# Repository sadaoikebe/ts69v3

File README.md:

# TS69V3 親指シフト入力に使える一体型 65% キーボード

## 特徴

オープンソースの親指シフトキーボードです。

* オープンソース基板（誰でもJLCPCBでオーダー可能！）
* 3Dプリントケース（誰でもJLCPCBで略）
* 一般的なキーボード部品で組み立て可能

## キーボード配列

* US / JP 両対応
* 矢印キーあり
* 対応する親指シフトファームウェアあり [ts69v3 firmware](https://github.com/sadaoikebe/qmk_firmware/tree/master/keyboards/ts69/v3)
* 親指シフト対応、親指キーB下割れ
* 親指キーに3u/2.75u/2.25uのキーキャップの任意の組み合わせが使用できる
* QMK対応

## 物理配列

本PCBで対応する物理配列を以下で解説します。代表的なものは以下の2通りです。

### US配列

<!--
["Esc\n\n~\n`","!\n1","@\n2","#\n3","$\n4","%\n5","^\n6","&\n7","*\n8","(\n9",")\n0","_\n-","+\n=",{w:2},"Backspace","Home"],
[{w:1.5},"Tab","Q","W","E","R","T","Y","U","I","O","P","{\n[","}\n]",{w:1.5},"|\n\\","PgUp"],
[{w:1.75},"Ctrl","A","S","D","F","G","H","J","K","L",":\n;","\"\n'",{w:2.25},"Enter","PgUp"],
[{w:2.25},"Shift","Z","X","C","V","B","N","M","<\n,",">\n.","?\n/",{w:1.75},"Shift","Up","End"],
[{a:7,w:1.25},"",{w:1.25},"",{w:1.25},"",{w:3},"3u 左親指",{w:3},"3u 右親指",{w:1.25},"","","","","",""],
-->

### JP配列
 
<!--
["Esc\n\n~\n`","!\n1","\"\n2","#\n3","$\n4","%\n5","&\n6","'\n7","(\n8",")\n9","\n0","=\n-","~\n^","|\n\\","BS","Home"],
[{w:1.5},"Tab","Q","W","E","R","T","Y","U","I","O","P","`\n@","{\n[",{x:0.25,w:1.25,h:2,w2:1.5,h2:1,x2:-0.25},"Enter","PgUp"],
[{w:1.75},"Ctrl","A","S","D","F","G","H","J","K","L","+\n;","*\n:","}\n]",{x:1.25},"PgDn"],
[{w:2},"Shift","Z","X","C","V","B","N","M","<\n,",">\n.","?\n/","_","Shift","Up","End"],
[{w:1.25},"",{w:1.25},"","","無変換",{w:2.25},"",{w:2.25},"","変換","カタ\nひら","","","","",""],
-->
JP配列のキー数を再現する場合、図のようにShiftの行は左に0.25u移動して、2u左小指シフト/1u右小指シフトを使用します。  
2.25u/1.75uの小指シフトを用いたければ、"_"(アンダースコア)のキーをあきらめてFnキー併用などして入力するようにするとよいでしょう。この場合Shiftの行の物理配列はUS配列と同様になります。  

### 親指シフトキーの選択肢

最下段は使用する親指キーの長さにより割り当てを選択できます。
キーキャップセットによっては、含まれるスペースバーの種類に制約があるけど、できるだけ対応できるようにしました。左右で違う長さの親指キーを使うこともできます。  
2.25uを使用すると、キーが一つ増えます。JP配列の場合は無変換や変換キーを割り当てることを想定しています。US配列の場合はお好みのキーを割り当てられます。

<!--
[{a:7,w:1.25},"",{w:1.25},"",{w:1.25},"",{w:3},"3u 左親指",{w:3},"3u 右親指",{w:1.25},"","","","","",""],
[{w:1.25},"",{w:1.25},"",{w:1.5},"",{w:2.75},"2.75u 左親指",{w:2.75},"2.75u 右親指",{w:1.25},"",{w:1.25},"","","","",""],
[{w:1.25},"",{w:1.25},"","","無変換",{w:2.25},"2.25u 左親指",{w:2.25},"2.25u 左親指","変換","","","","","",""]
-->

### 最上段のBackspaceキー

最上段に2u Backspaceを用いるかわりに、2つのキーを割りあてることができます。最上段にBackspaceを割り当てない場合、一般的に上から2段目のキーにBackspaceを割り当てるようです。(HHKB-likeなレイアウトです)

<!--
["Esc\n\n~\n`","!\n1","@\n2","#\n3","$\n4","%\n5","^\n6","&\n7","*\n8","(\n9",")\n0","_\n-","+\n=",{w:2},"Backspace","Home"],
["Esc","!\n1","@\n2","#\n3","$\n4","%\n5","^\n6","&\n7","*\n8","(\n9",")\n0","_\n-","+\n=","|\n\\","~\n`","Home"],
-->

# BOM

Item |ソース | 数量 |  備考
:--- | :--- | :--- | :---
TS69V3 PCBA | [JLCPCB PCBA](pcb/) | 1 |
ケース | [3D Printed](case/) | 1 | 
定位板 | [Laser Cut Brass](plate/) | 1 | t=1.5mm アクリルでも良いが割れやすい
ヒートセット M3x6mmx4.6mm | [AliEx/淘宝等](https://www.aliexpress.com/item/1005002288716120.html) | 10 | 長さは6mmでなくても良い
M3 円頭六角ボルト 6mm | | 10 |  
クッション 2mm厚 x 60mm x 4mm | | 16 | Poron/EVAフォーム等
Pro Micro | [Shigezone等](https://www.shigezone.com/product/arduino-pro-micro/) | 1 | USB-Cタイプがおすすめ
ピンヘッダ 12pin 2.54ピッチ | 電子工作ショップ等 | 2 |
キースイッチ | AliEx/淘宝/自キ専門店等 | 配列によって69〜73個 | 何でもOK(kailh box 白軸がおすすめ)
2u スタビライザー | AliEx/淘宝/自キ専門店等 | 配列によって2〜5個 | 採用したPlateの種類に応じて Plate Mount / PCB Mountを選択
3u スタビライザー | AliEx/淘宝/自キ専門店等 | 配列によって0〜2個 | 
キーキャップ | AliEx/淘宝/自キ専門店等 | 1set | 3u/2.75u/2.25u等の親指キーが計2つ必要

## 組み立て工程

Pro Microを裏側実装する関係で、実装の順番を間違えると*かなり*面倒
1. 基板にスタビライザーを取り付け
2. 基板にピンヘッダを半田付け
3. 定位板に四隅のキースイッチを通す。Pro Microを実装する面の裏のキー(ESCと1)は2つともキースイッチをハンダ付けする。(以後取り外しが極めて難しい)
4. Pro Microを取り付け、キースイッチを取り付け

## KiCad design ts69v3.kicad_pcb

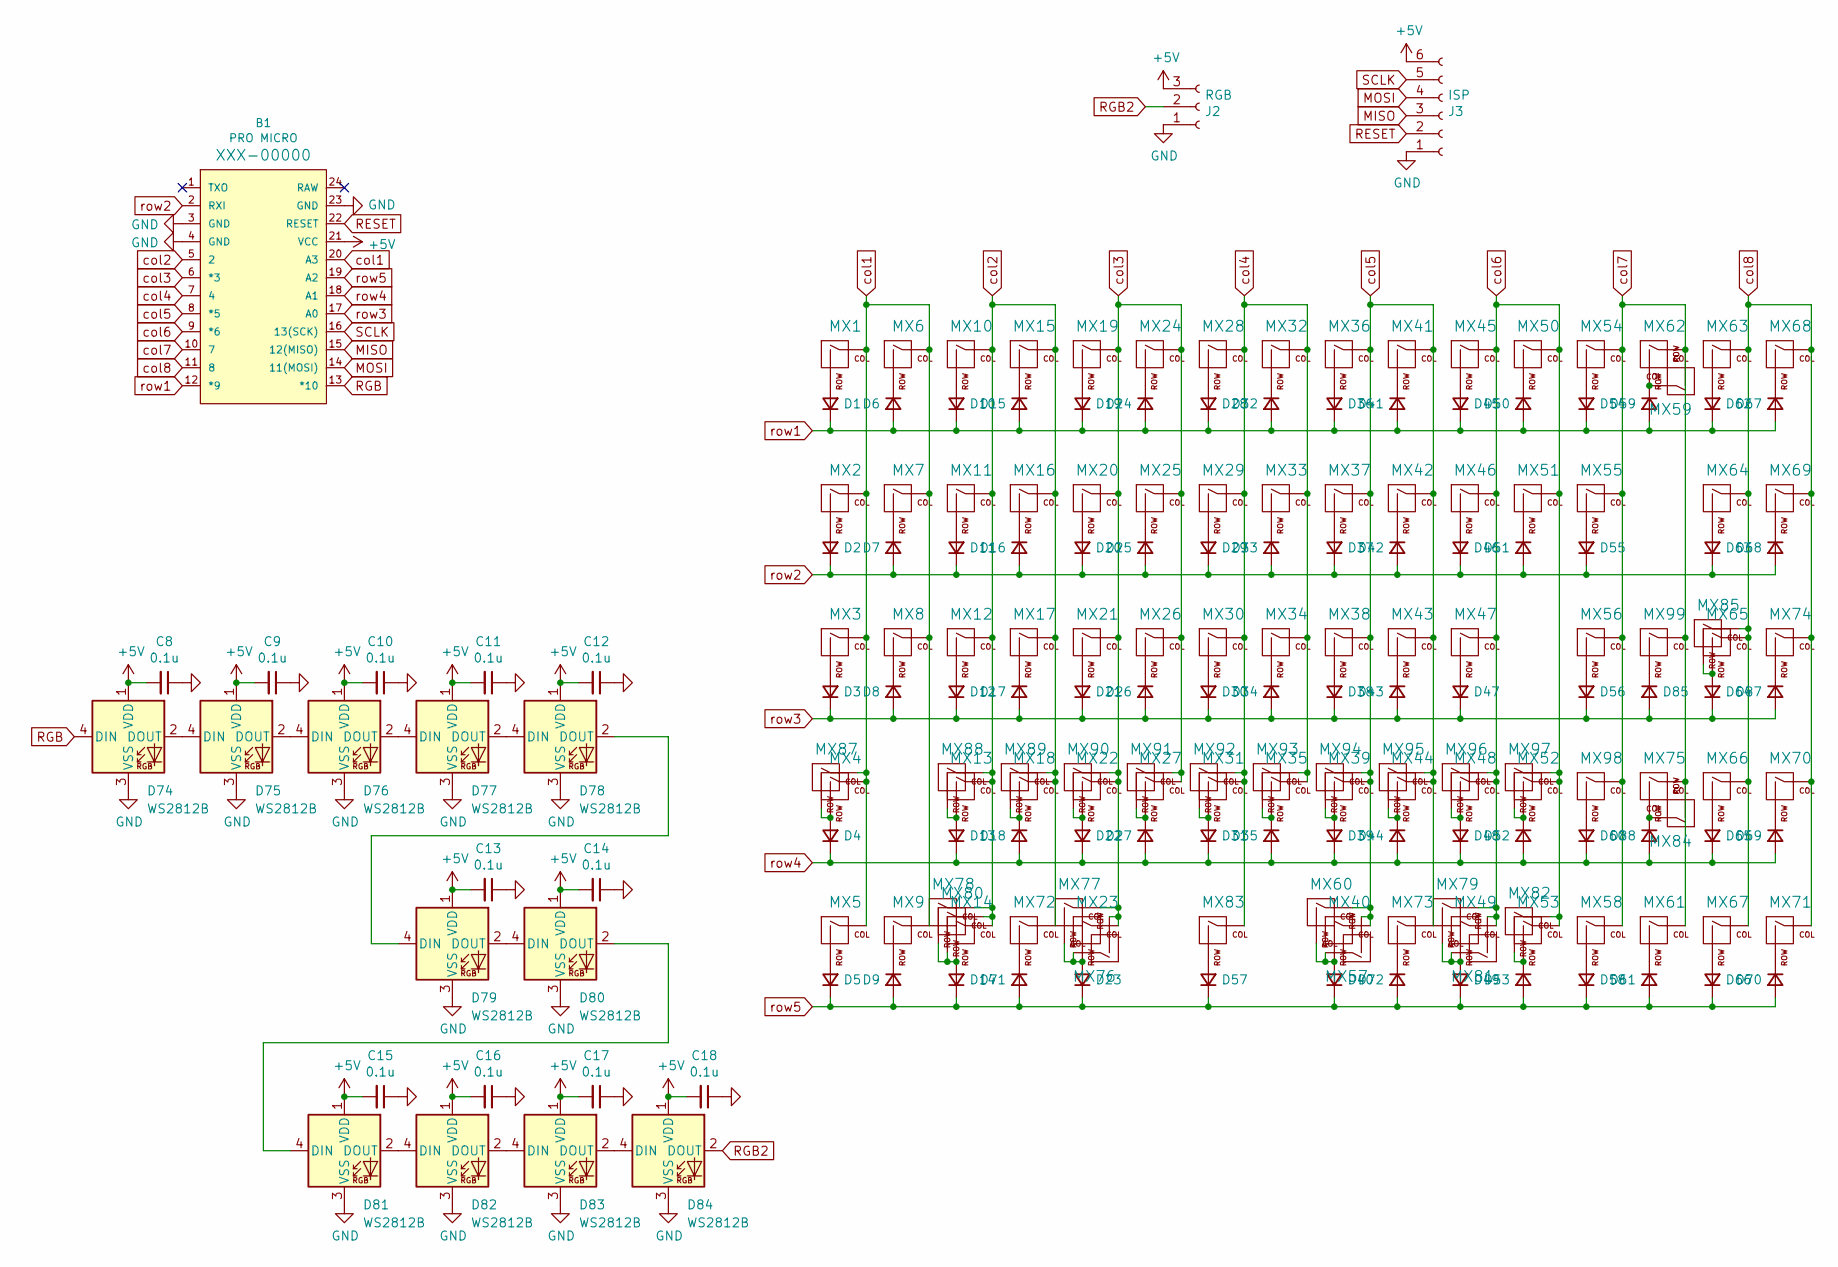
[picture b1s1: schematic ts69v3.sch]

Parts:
B1: PRO MICRO; PROMICRO_CONTHRU
C8, C9, C10, C11, C12, C13, C14, C15, C16, C17, C18: 0.1u; C_0402_1005Metric; LCSC C60474
D1, D2, D3, D4, D5, D6, D7, D8, D9, D10, D11, D12, D13, D14, D15, D16, D17, D18, D19, D20, D21, D22, D23, D24, D25, D26, D27, D28, D29, D30, D31, D32, D33, D34, D35, D36, D37, D38, D39, D40, D41, D42, D43, D44, D45, D46, D47, D48, D49, D50, D51, D52, D53, D54, D55, D56, D57, D58, D59, D61, D62, D63, D64, D65, D66, D67, D68, D69, D70, D71, D72, D87, D88: D; D_SOD-123; LCSC C84367
D60, D85: D; D_SOD-123
D74, D75, D76, D77, D78, D79, D80, D81, D82, D83, D84: WS2812B; LED_WS2812B_PLCC4_5.0x5.0mm_P3.2mm; LCSC C114586
J2: RGB; PinHeader_1x03_P2.00mm_Vertical
J3: ISP; PinHeader_1x06_P2.00mm_Vertical
MX1, MX6, MX7, MX8, MX10, MX11, MX12, MX13, MX15, MX16, MX17, MX18, MX19, MX20, MX21, MX22, MX24, MX25, MX26, MX27, MX28, MX29, MX30, MX31, MX32, MX33, MX34, MX35, MX36, MX37, MX38, MX39, MX41, MX42, MX43, MX44, MX45, MX46, MX47, MX48, MX50, MX51, MX52, MX53, MX54, MX55, MX56, MX58, MX59, MX61, MX63, MX66, MX67, MX68, MX69, MX70, MX71, MX72, MX73, MX74, MX79, MX80, MX84, MX88, MX89, MX90, MX91, MX92, MX93, MX94, MX95, MX96, MX97, MX98, MX99: MX-NoLED; MXOnly-1U-NoLED
MX2, MX64, MX78: MX-NoLED; MXOnly-1.5U-NoLED
MX3, MX75: MX-NoLED; MXOnly-1.75U-NoLED
MX4, MX65: MX-NoLED; MXOnly-2.25U-NoLED
MX5, MX9, MX14, MX49, MX81, MX82: MX-NoLED; MXOnly-1.25U-NoLED
MX23, MX40: MX-NoLED; MXOnly-3U-ReversedStabilizers-NoLED
MX57, MX76: MX-NoLED; MXOnly-2.25U-ReversedStabilizers-NoLED
MX60, MX77: MX-NoLED; MXOnly-2.75U-ReversedStabilizers-NoLED
MX62, MX87: MX-NoLED; MXOnly-2U-NoLED
MX83: MX-NoLED; MXOnly-6.25U-ReversedStabilizers-NoLED
MX85: MX-NoLED; MXOnly-2U-ReversedVerticalStabilizers-NoLED

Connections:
+5V: B1.21 (VCC), C8.2, C9.2, C10.2, C11.2, C12.2, C13.2, C14.2, C15.2, C16.2, C17.2, C18.2, D74.1 (VDD), D75.1 (VDD), D76.1 (VDD), D77.1 (VDD), D78.1 (VDD), D79.1 (VDD), D80.1 (VDD), D81.1 (VDD), D82.1 (VDD), D83.1 (VDD), D84.1 (VDD), J2.3, J3.6
GND: B1.3 (GND), B1.4 (GND), B1.23 (GND), C8.1, C9.1, C10.1, C11.1, C12.1, C13.1, C14.1, C15.1, C16.1, C17.1, C18.1, D74.3 (VSS), D75.3 (VSS), D76.3 (VSS), D77.3 (VSS), D78.3 (VSS), D79.3 (VSS), D80.3 (VSS), D81.3 (VSS), D82.3 (VSS), D83.3 (VSS), D84.3 (VSS), J2.1, J3.1
MISO: B1.15 (12(MISO)), J3.3
MOSI: B1.14 (11(MOSI)), J3.4
unnamed: D1.2 (A), MX1.2 (ROW)
unnamed: D2.2 (A), MX2.2 (ROW)
unnamed: D3.2 (A), MX3.2 (ROW)
unnamed: D4.2 (A), MX4.2 (ROW), MX87.2 (ROW)
unnamed: D5.2 (A), MX5.2 (ROW)
unnamed: D6.1 (K), MX6.2 (ROW)
unnamed: D7.1 (K), MX7.2 (ROW)
unnamed: D8.1 (K), MX8.2 (ROW)
unnamed: D9.1 (K), MX9.2 (ROW)
unnamed: D10.2 (A), MX10.2 (ROW)
unnamed: D11.2 (A), MX11.2 (ROW)
unnamed: D12.2 (A), MX12.2 (ROW)
unnamed: D13.2 (A), MX13.2 (ROW), MX88.2 (ROW)
unnamed: D14.2 (A), MX14.2 (ROW), MX78.2 (ROW), MX80.2 (ROW)
unnamed: D15.1 (K), MX15.2 (ROW)
unnamed: D16.1 (K), MX16.2 (ROW)
unnamed: D17.1 (K), MX17.2 (ROW)
unnamed: D18.1 (K), MX18.2 (ROW), MX89.2 (ROW)
unnamed: D19.2 (A), MX19.2 (ROW)
unnamed: D20.2 (A), MX20.2 (ROW)
unnamed: D21.2 (A), MX21.2 (ROW)
unnamed: D22.2 (A), MX22.2 (ROW), MX90.2 (ROW)
unnamed: D23.2 (A), MX23.2 (ROW), MX76.1 (COL), MX77.2 (ROW)
unnamed: D24.1 (K), MX24.2 (ROW)
unnamed: D25.1 (K), MX25.2 (ROW)
unnamed: D26.1 (K), MX26.2 (ROW)
unnamed: D27.1 (K), MX27.2 (ROW), MX91.2 (ROW)
unnamed: D28.2 (A), MX28.2 (ROW)
unnamed: D29.2 (A), MX29.2 (ROW)
unnamed: D30.2 (A), MX30.2 (ROW)
unnamed: D31.2 (A), MX31.2 (ROW), MX92.2 (ROW)
unnamed: D32.1 (K), MX32.2 (ROW)
unnamed: D33.1 (K), MX33.2 (ROW)
unnamed: D34.1 (K), MX34.2 (ROW)
unnamed: D35.1 (K), MX35.2 (ROW), MX93.2 (ROW)
unnamed: D36.2 (A), MX36.2 (ROW)
unnamed: D37.2 (A), MX37.2 (ROW)
unnamed: D38.2 (A), MX38.2 (ROW)
unnamed: D39.2 (A), MX39.2 (ROW), MX94.2 (ROW)
unnamed: D40.2 (A), MX40.2 (ROW), MX57.1 (COL), MX60.2 (ROW)
unnamed: D41.1 (K), MX41.2 (ROW)
unnamed: D42.1 (K), MX42.2 (ROW)
unnamed: D43.1 (K), MX43.2 (ROW)
unnamed: D44.1 (K), MX44.2 (ROW), MX95.2 (ROW)
unnamed: D45.2 (A), MX45.2 (ROW)
unnamed: D46.2 (A), MX46.2 (ROW)
unnamed: D47.2 (A), MX47.2 (ROW)
unnamed: D48.2 (A), MX48.2 (ROW), MX96.2 (ROW)
unnamed: D49.2 (A), MX49.2 (ROW), MX79.2 (ROW), MX81.1 (COL)
unnamed: D50.1 (K), MX50.2 (ROW)
unnamed: D51.1 (K), MX51.2 (ROW)
unnamed: D52.1 (K), MX52.2 (ROW), MX97.2 (ROW)
unnamed: D53.1 (K), MX53.2 (ROW), MX82.2 (ROW)
unnamed: D54.2 (A), MX54.2 (ROW)
unnamed: D55.2 (A), MX55.2 (ROW)
unnamed: D56.2 (A), MX56.2 (ROW)
unnamed: D57.2 (A), MX83.2 (ROW)
unnamed: D58.2 (A), MX58.2 (ROW)
unnamed: D59.1 (K), MX59.1 (COL), MX62.2 (ROW)
unnamed: D60.2 (A), MX98.2 (ROW)
unnamed: D61.1 (K), MX61.2 (ROW)
unnamed: D62.2 (A), MX63.2 (ROW)
unnamed: D63.2 (A), MX64.2 (ROW)
unnamed: D64.2 (A), MX65.2 (ROW), MX85.2 (ROW)
unnamed: D65.2 (A), MX66.2 (ROW)
unnamed: D66.2 (A), MX67.2 (ROW)
unnamed: D67.1 (K), MX68.2 (ROW)
unnamed: D68.1 (K), MX69.2 (ROW)
unnamed: D69.1 (K), MX70.2 (ROW)
unnamed: D70.1 (K), MX71.2 (ROW)
unnamed: D71.1 (K), MX72.2 (ROW)
unnamed: D72.1 (K), MX73.2 (ROW)
unnamed: D74.2 (DOUT), D75.4 (DIN)
unnamed: D75.2 (DOUT), D76.4 (DIN)
unnamed: D76.2 (DOUT), D77.4 (DIN)
unnamed: D77.2 (DOUT), D78.4 (DIN)
unnamed: D78.2 (DOUT), D79.4 (DIN)
unnamed: D79.2 (DOUT), D80.4 (DIN)
unnamed: D80.2 (DOUT), D81.4 (DIN)
unnamed: D81.2 (DOUT), D82.4 (DIN)
unnamed: D82.2 (DOUT), D83.4 (DIN)
unnamed: D83.2 (DOUT), D84.4 (DIN)
unnamed: D85.1 (K), MX99.2 (ROW)
unnamed: D87.1 (K), MX74.2 (ROW)
unnamed: D88.1 (K), MX75.2 (ROW), MX84.1 (COL)
RESET: B1.22 (RESET), J3.2
RGB: B1.13 (*10), D74.4 (DIN)
RGB2: D84.2 (DOUT), J2.2
SCLK: B1.16 (13(SCK)), J3.5
col1: B1.20 (A3), MX1.1 (COL), MX2.1 (COL), MX3.1 (COL), MX4.1 (COL), MX5.1 (COL), MX6.1 (COL), MX7.1 (COL), MX8.1 (COL), MX9.1 (COL), MX87.1 (COL)
col2: B1.5 (2), MX10.1 (COL), MX11.1 (COL), MX12.1 (COL), MX13.1 (COL), MX14.1 (COL), MX15.1 (COL), MX16.1 (COL), MX17.1 (COL), MX18.1 (COL), MX72.1 (COL), MX78.1 (COL), MX80.1 (COL), MX88.1 (COL), MX89.1 (COL)
col3: B1.6 (*3), MX19.1 (COL), MX20.1 (COL), MX21.1 (COL), MX22.1 (COL), MX23.1 (COL), MX24.1 (COL), MX25.1 (COL), MX26.1 (COL), MX27.1 (COL), MX76.2 (ROW), MX77.1 (COL), MX90.1 (COL), MX91.1 (COL)
col4: B1.7 (4), MX28.1 (COL), MX29.1 (COL), MX30.1 (COL), MX31.1 (COL), MX32.1 (COL), MX33.1 (COL), MX34.1 (COL), MX35.1 (COL), MX83.1 (COL), MX92.1 (COL), MX93.1 (COL)
col5: B1.8 (*5), MX36.1 (COL), MX37.1 (COL), MX38.1 (COL), MX39.1 (COL), MX40.1 (COL), MX41.1 (COL), MX42.1 (COL), MX43.1 (COL), MX44.1 (COL), MX57.2 (ROW), MX60.1 (COL), MX73.1 (COL), MX94.1 (COL), MX95.1 (COL)
col6: B1.9 (*6), MX45.1 (COL), MX46.1 (COL), MX47.1 (COL), MX48.1 (COL), MX49.1 (COL), MX50.1 (COL), MX51.1 (COL), MX52.1 (COL), MX53.1 (COL), MX79.1 (COL), MX81.2 (ROW), MX82.1 (COL), MX96.1 (COL), MX97.1 (COL)
col7: B1.10 (7), MX54.1 (COL), MX55.1 (COL), MX56.1 (COL), MX58.1 (COL), MX59.2 (ROW), MX61.1 (COL), MX62.1 (COL), MX75.1 (COL), MX84.2 (ROW), MX98.1 (COL), MX99.1 (COL)
col8: B1.11 (8), MX63.1 (COL), MX64.1 (COL), MX65.1 (COL), MX66.1 (COL), MX67.1 (COL), MX68.1 (COL), MX69.1 (COL), MX70.1 (COL), MX71.1 (COL), MX74.1 (COL), MX85.1 (COL)
row1: B1.12 (*9), D1.1 (K), D6.2 (A), D10.1 (K), D15.2 (A), D19.1 (K), D24.2 (A), D28.1 (K), D32.2 (A), D36.1 (K), D41.2 (A), D45.1 (K), D50.2 (A), D54.1 (K), D59.2 (A), D62.1 (K), D67.2 (A)
row2: B1.2 (RXI), D2.1 (K), D7.2 (A), D11.1 (K), D16.2 (A), D20.1 (K), D25.2 (A), D29.1 (K), D33.2 (A), D37.1 (K), D42.2 (A), D46.1 (K), D51.2 (A), D55.1 (K), D63.1 (K), D68.2 (A)
row3: B1.17 (A0), D3.1 (K), D8.2 (A), D12.1 (K), D17.2 (A), D21.1 (K), D26.2 (A), D30.1 (K), D34.2 (A), D38.1 (K), D43.2 (A), D47.1 (K), D56.1 (K), D64.1 (K), D85.2 (A), D87.2 (A)
row4: B1.18 (A1), D4.1 (K), D13.1 (K), D18.2 (A), D22.1 (K), D27.2 (A), D31.1 (K), D35.2 (A), D39.1 (K), D44.2 (A), D48.1 (K), D52.2 (A), D60.1 (K), D65.1 (K), D69.2 (A), D88.2 (A)
row5: B1.19 (A2), D5.1 (K), D9.2 (A), D14.1 (K), D23.1 (K), D40.1 (K), D49.1 (K), D53.2 (A), D57.1 (K), D58.1 (K), D61.2 (A), D66.1 (K), D70.2 (A), D71.2 (A), D72.2 (A)

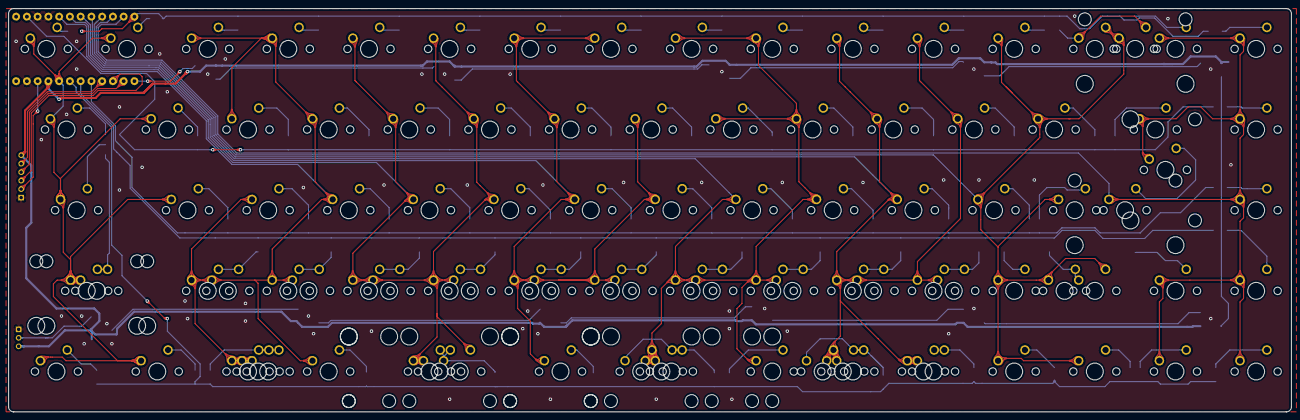
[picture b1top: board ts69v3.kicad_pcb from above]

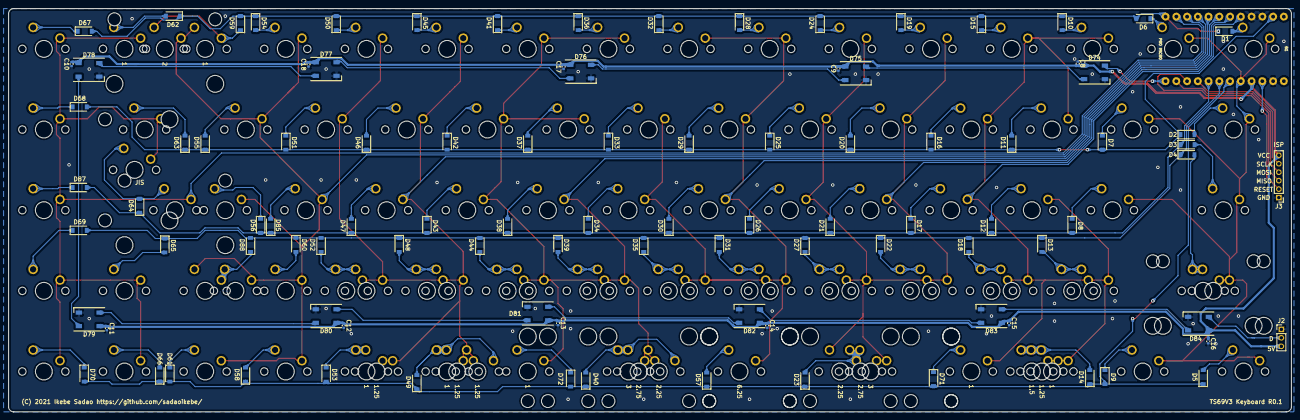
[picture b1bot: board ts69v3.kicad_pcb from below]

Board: 2 copper layers, 303.0 x 95.3 mm, 198 parts (100 on the bottom side), 106 nets.

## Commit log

2021-09-25 add readme
2021-09-25 jlcpcb order
2021-09-25 add readme, move to subdirectory
2021-09-30 update description
2022-08-06 add bom table
2022-08-06 fix bom table
2022-08-06 table still not working
2022-08-06 need better previewer...
2022-08-06 added cusion to BOM
2022-08-06 fix bom
2022-08-06 add plate
2022-08-06 fix dxf scale
2022-08-10 add case
2022-08-10 add case link
2022-08-11 add case stl and plate thickness
2022-08-11 separate lid
2022-08-11 add separate base
2022-08-11 base depth and split groove
2022-08-11 depth adjustment
2022-08-11 old logo remnant
2022-08-12 change rubber preload
2022-08-28 bom update
2022-11-07 add desc
2022-11-07 add pic

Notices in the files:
ts69v3.kicad_pcb:
(C) 2021 Ikebe Sadao https://github.com/sadaoikebe
